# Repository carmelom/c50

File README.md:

# C-50
## v. 1.1
Digital oscillator synchronized to the mains frequency

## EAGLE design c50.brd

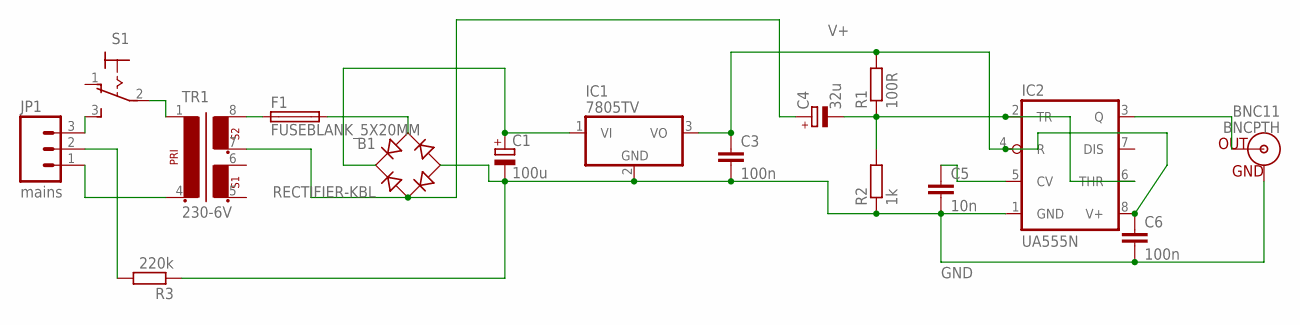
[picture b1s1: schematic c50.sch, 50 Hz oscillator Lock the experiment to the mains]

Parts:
B1: RECTIFIER-KBL; B-DIL
BNC11: BNCPTH; BNC
C1: 100u; E2,5-7
C3, C6: 100n; C050-024X044
C4: 32u; E5-13
C5: 10n; C050-024X044
F1: FUSEBLANK_5X20MM; FUSE_HOLDER_5X20MM
IC1: 7805TV; TO220V
IC2: UA555N; DIL08
JP1: mains; SCREWTERMINAL-5MM-3
R1: 100R; 0207/10
R2: 1k; 0207/10
R3: 220k; 0207/10
S1: 320-916
TR1: 230-6V; EE20-2

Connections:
GND: B1.-, BNC11.GND, C1.-, C3.2, C5.2, C6.2, IC1.2 (GND), IC2.1 (GND), R2.1, R3.1
unnamed: S1.2, TR1.1
unnamed: B1.AC2, C4.+, TR1.7 (5)
unnamed: JP1.1, TR1.4 (2)
unnamed: JP1.2, R3.2
unnamed: B1.+, C1.+, IC1.1 (VI)
unnamed: F1.1, TR1.8 (6)
unnamed: C5.1, IC2.5 (CV)
unnamed: C4.-, IC2.2 (TR), IC2.6 (THR), R1.1, R2.2
unnamed: BNC11.S (OUT), IC2.3 (Q)
unnamed: JP1.3, S1.3 (S)
unnamed: B1.AC1, F1.2
V+: C3.1, C6.1, IC1.3 (VO), IC2.4 (R), IC2.8 (V+), R1.2

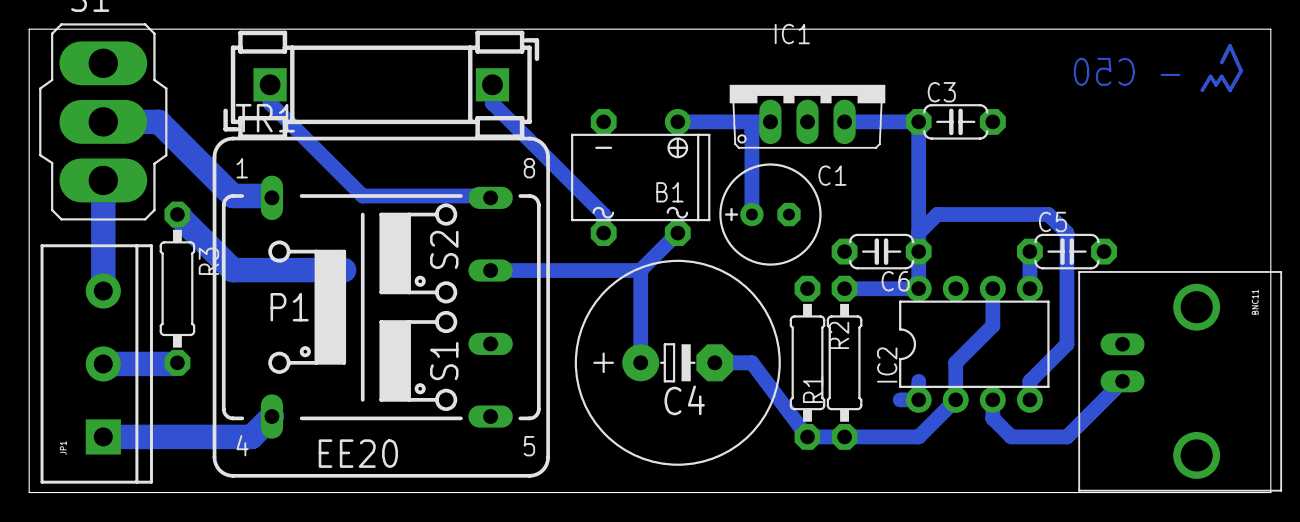
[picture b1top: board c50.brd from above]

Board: 2 copper layers, 85.1 x 31.8 mm, 16 parts (0 on the bottom side), 13 nets.

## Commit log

2015-12-15 Init repo
2015-12-15 Smaller transformer, DIL package for rectifier bridge. More compact design.
2015-12-15 Compact design.
2015-12-16 v 1.1: added switch gitignore updated with 'stuff' folder
2015-12-16 Big rename
2016-01-12 Final scheme with gerber project end
2016-01-12 Update to final design. Send gerber files to the workshop.
2016-01-14 Signature added.
2016-01-25 Modified gerbers, sistemati drill e holes. Routing da finire.
2016-01-26 Finished (maybe)

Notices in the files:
parts and their libraries:
SparkFun-Connectors: Licensing: Creative Commons ShareAlike 4.0 International - https://creativecommons.org/licenses/by-sa/4.0
